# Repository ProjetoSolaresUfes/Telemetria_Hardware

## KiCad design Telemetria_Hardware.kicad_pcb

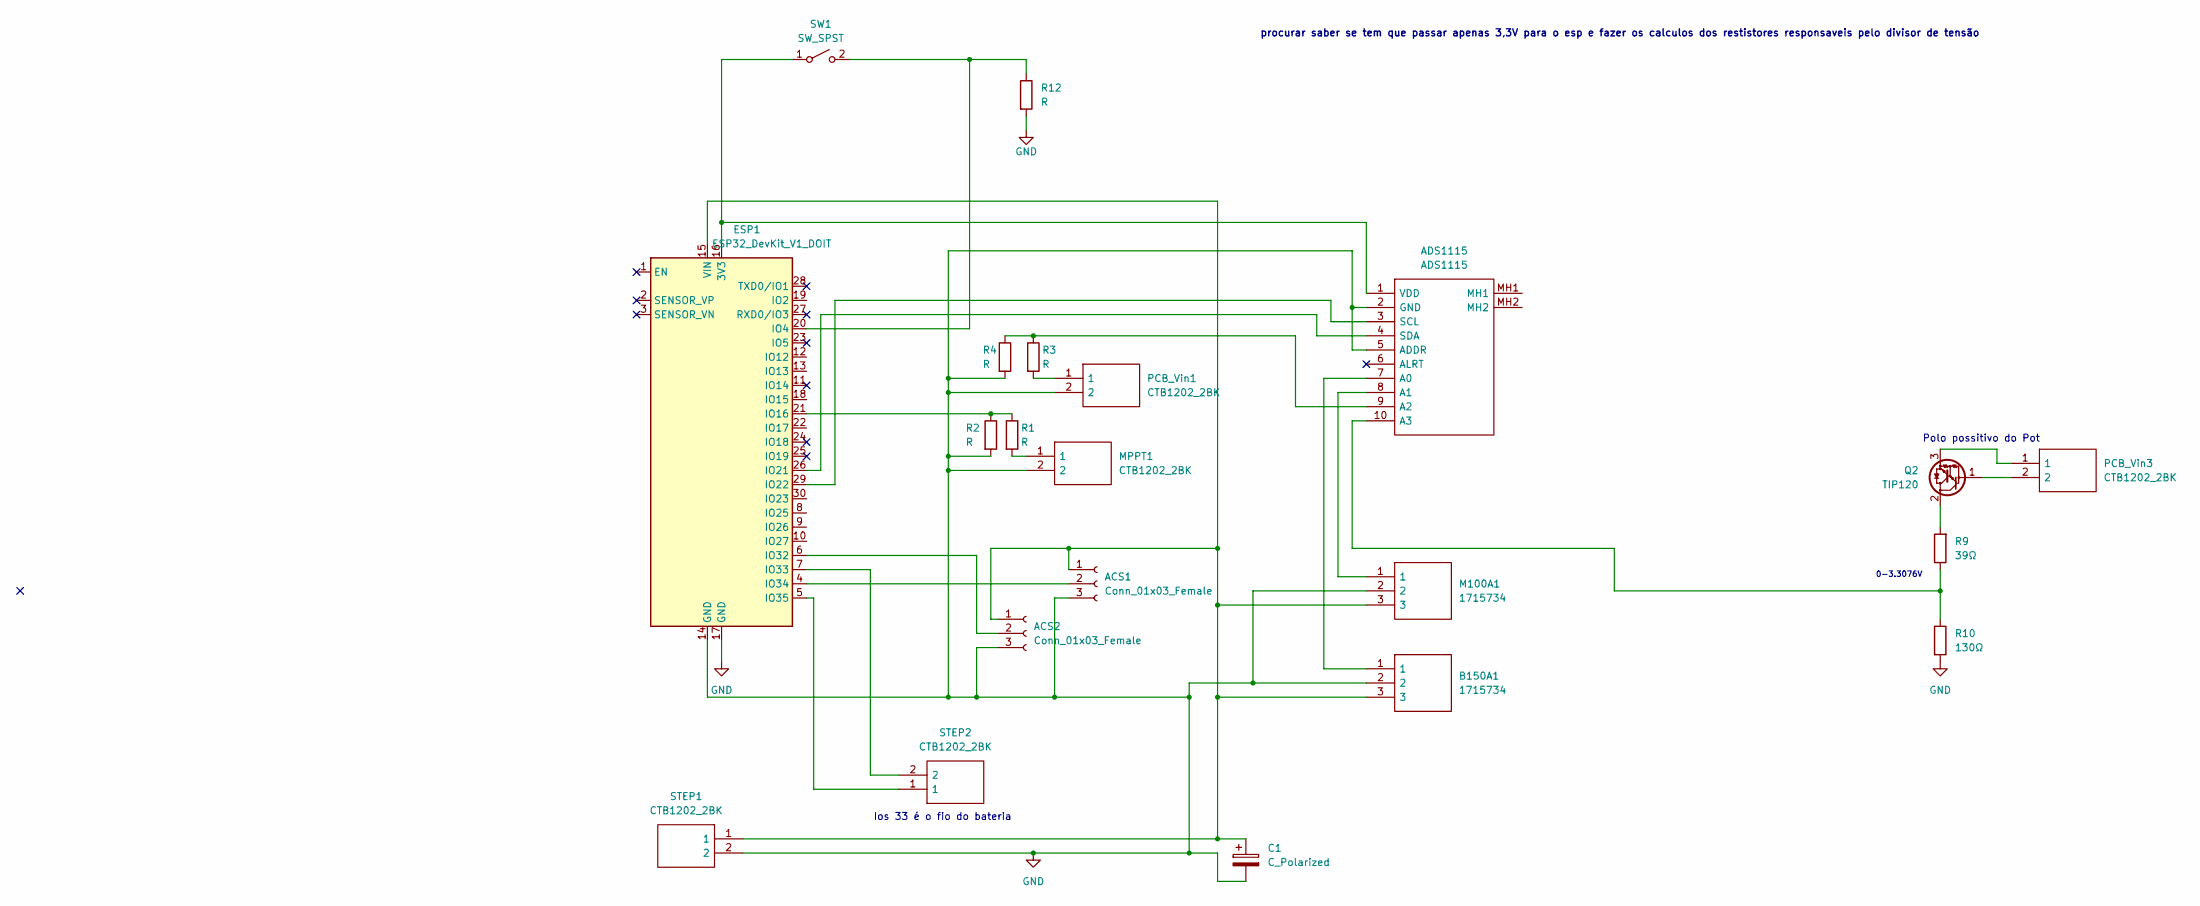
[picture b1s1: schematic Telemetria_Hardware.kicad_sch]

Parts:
ACS1, ACS2: Conn_01x03_Female; PinSocket_1x03_P2.54mm_Vertical
ADS1115: ADS1115; Manufacturer_Part_Number ADS1115
B150A1: 1715734; TerminalBlock_bornier-3_P5.08mm; Manufacturer_Part_Number 1715734
C1: C_Polarized; C_Radial_D6.3mm_H11.0mm_P2.50mm
ESP1: ESP32_DevKit_V1_DOIT; esp32_devkit_v1_doit
M100A1: 1715734; TerminalBlock_bornier-3_P5.08mm; Manufacturer_Part_Number 1715734
MPPT1: CTB1202_2BK; TerminalBlock_bornier-2_P5.08mm; Manufacturer_Part_Number CTB1202/2BK
PCB_Vin1, PCB_Vin3: CTB1202_2BK; TerminalBlock_bornier-2_P5.08mm; Manufacturer_Part_Number CTB1202/2BK
Q2: TIP120; TO-220-3_Vertical
R1, R2, R3, R4, R12: R; R_Axial_DIN0207_L6.3mm_D2.5mm_P10.16mm_Horizontal
R9: 39Ω; R_Axial_DIN0207_L6.3mm_D2.5mm_P10.16mm_Horizontal
R10: 130Ω; R_Axial_DIN0207_L6.3mm_D2.5mm_P10.16mm_Horizontal
STEP1, STEP2: CTB1202_2BK; TerminalBlock_bornier-2_P5.08mm; Manufacturer_Part_Number CTB1202/2BK
SW1: SW_SPST; SW_DIP_SPSTx01_Slide_9.78x4.72mm_W7.62mm_P2.54mm

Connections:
GND: ACS1.3, ACS2.3, ADS1115.2 (GND), ADS1115.5 (ADDR), B150A1.2, C1.2, ESP1.14 (GND), ESP1.17 (GND), M100A1.2, MPPT1.2, PCB_Vin1.2, R2.2, R4.2, R10.2, R12.2, STEP1.2; also elsewhere on the board
unnamed 1: ACS1.1, ACS2.1, B150A1.3, C1.1, ESP1.15 (VIN), M100A1.3, STEP1.1; also elsewhere on the board
unnamed 2: ACS1.2, ESP1.4 (IO34); also elsewhere on the board
unnamed 3: ACS2.2, ESP1.6 (IO32); also elsewhere on the board
unnamed: ADS1115.7 (A0), B150A1.1
unnamed: ADS1115.8 (A1), M100A1.1
unnamed: ADS1115.9 (A2), R3.1, R4.1
unnamed: ADS1115.10 (A3), R9.1, R10.1
unnamed 8: ADS1115.3 (SCL), ESP1.29 (IO22); also elsewhere on the board
unnamed 9: ADS1115.4 (SDA), ESP1.26 (IO21); also elsewhere on the board
unnamed 10: ADS1115.1 (VDD), ESP1.16 (3V3), SW1.1 (A); also elsewhere on the board
unnamed 11: ESP1.20 (IO4), R12.1, SW1.2 (B); also elsewhere on the board
unnamed: ESP1.21 (IO16), R1.1, R2.1
unnamed 13: ESP1.7 (IO33), STEP2.2; also elsewhere on the board
unnamed 14: ESP1.5 (IO35), STEP2.1; also elsewhere on the board
unnamed: MPPT1.1, R1.2
unnamed: PCB_Vin1.1, R3.2
unnamed: PCB_Vin3.2, Q2.1 (B)
unnamed: Q2.2 (C), R9.2
unnamed: PCB_Vin3.1, Q2.3 (E)

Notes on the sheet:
0-3.3076V
Ios 33 é o fio do bateria
procurar saber se tem que passar apenas 3,3V para o esp e fazer os calculos dos restistores responsaveis pelo divisor de tensão
Polo possitivo do Pot

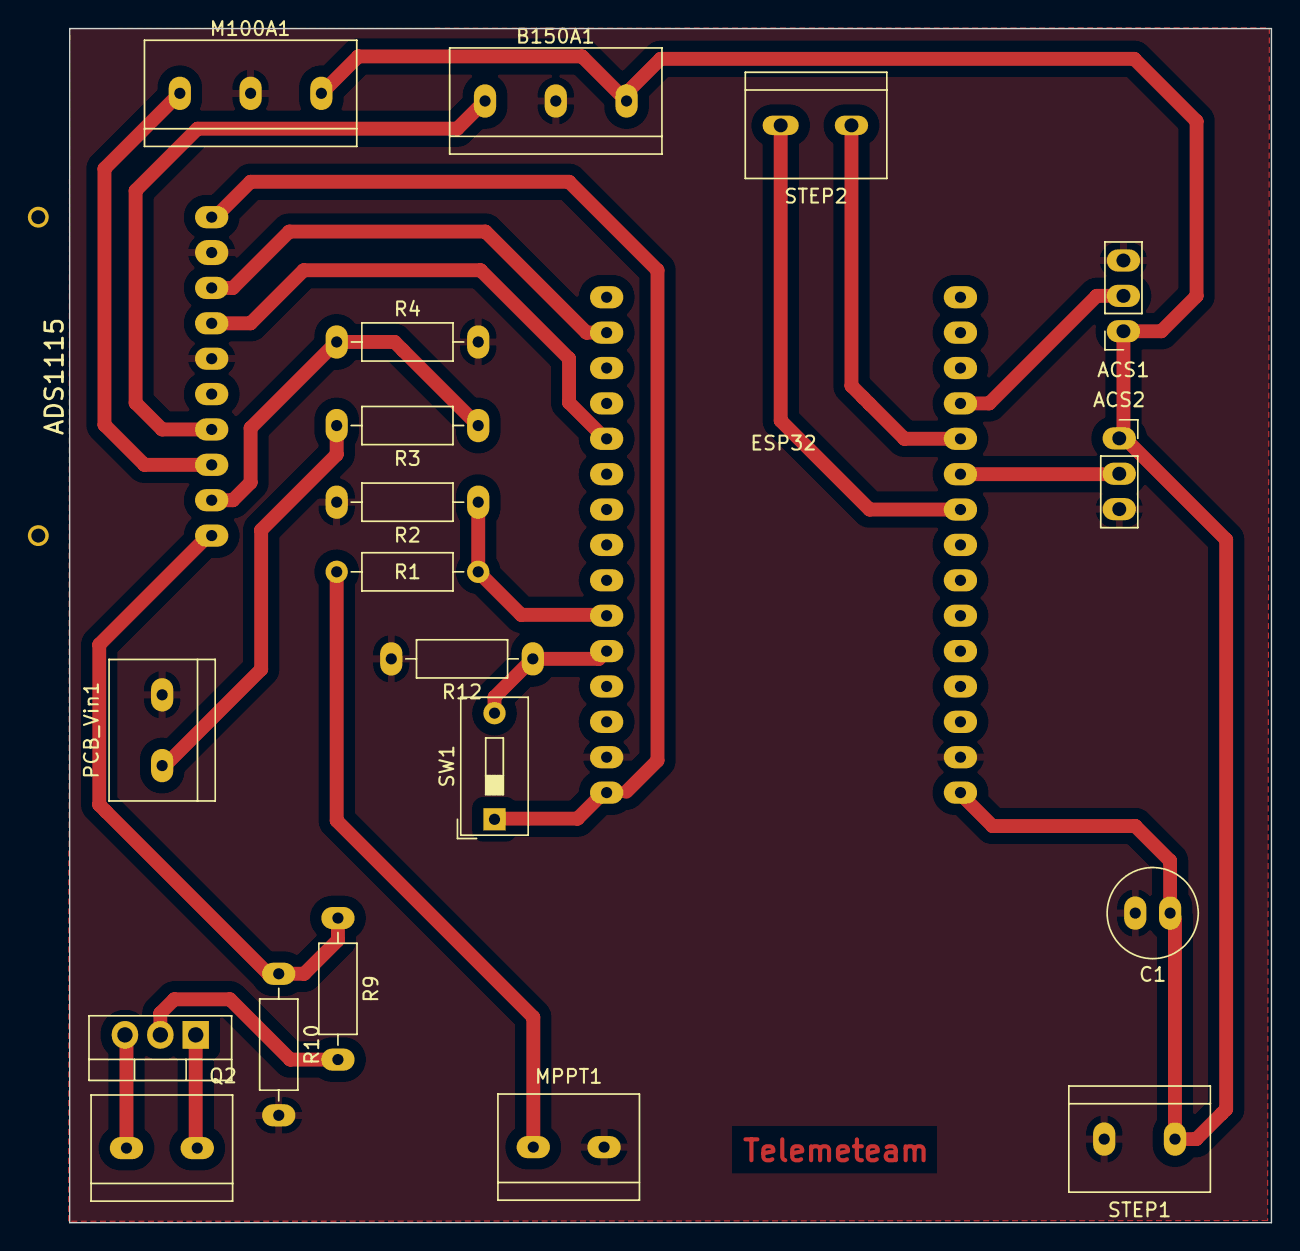
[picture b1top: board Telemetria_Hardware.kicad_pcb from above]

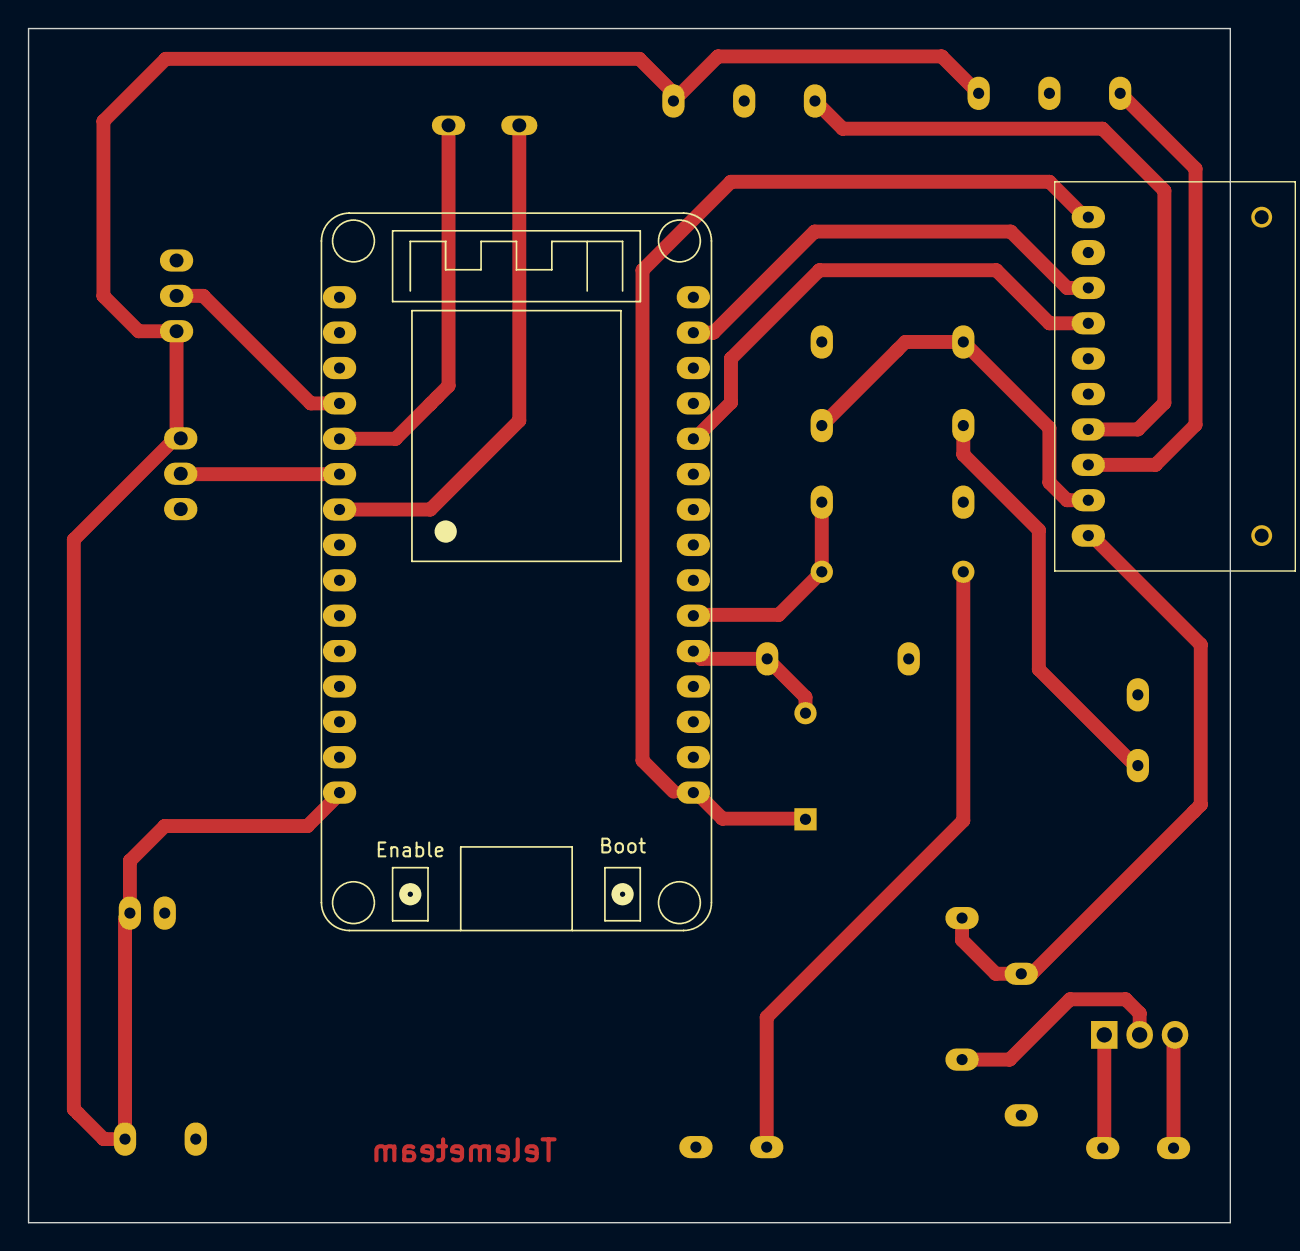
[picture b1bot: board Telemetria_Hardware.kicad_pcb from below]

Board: 2 copper layers, 86.3 x 85.7 mm, 21 parts (2 on the bottom side), 20 nets.

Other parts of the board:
ESP32: ESP32_DevKit_V1_DOIT; esp32_devkit_v1_doit

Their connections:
GND: ESP32.14 (GND), ESP32.17 (GND); also elsewhere on the board
unnamed 1: ESP32.15 (VIN); also elsewhere on the board
unnamed 2: ESP32.4 (IO34); also elsewhere on the board
unnamed 3: ESP32.6 (IO32); also elsewhere on the board
unnamed 8: ESP32.29 (IO22); also elsewhere on the board
unnamed 9: ESP32.26 (IO21); also elsewhere on the board
unnamed 10: ESP32.16 (3V3); also elsewhere on the board
unnamed 11: ESP32.20 (IO4); also elsewhere on the board
unnamed 13: ESP32.7 (IO33); also elsewhere on the board
unnamed 14: ESP32.5 (IO35); also elsewhere on the board

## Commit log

2023-10-03 Version 2023 - Niteroi
2023-10-03 pastas up
2023-12-06 Pequenas mudanças no 3D
2024-04-24 ads adicionado
2024-04-29 placa teste
2024-05-02 teste 2
2024-05-16 teste 3
2024-05-28 teste4
2024-06-04 sugestao
2024-06-28 teste 5
2024-06-28 teste 5 (certo)
2024-07-17 Mudanças pré DSB 2024
2024-07-17 Mudanças Pré DSB/2
